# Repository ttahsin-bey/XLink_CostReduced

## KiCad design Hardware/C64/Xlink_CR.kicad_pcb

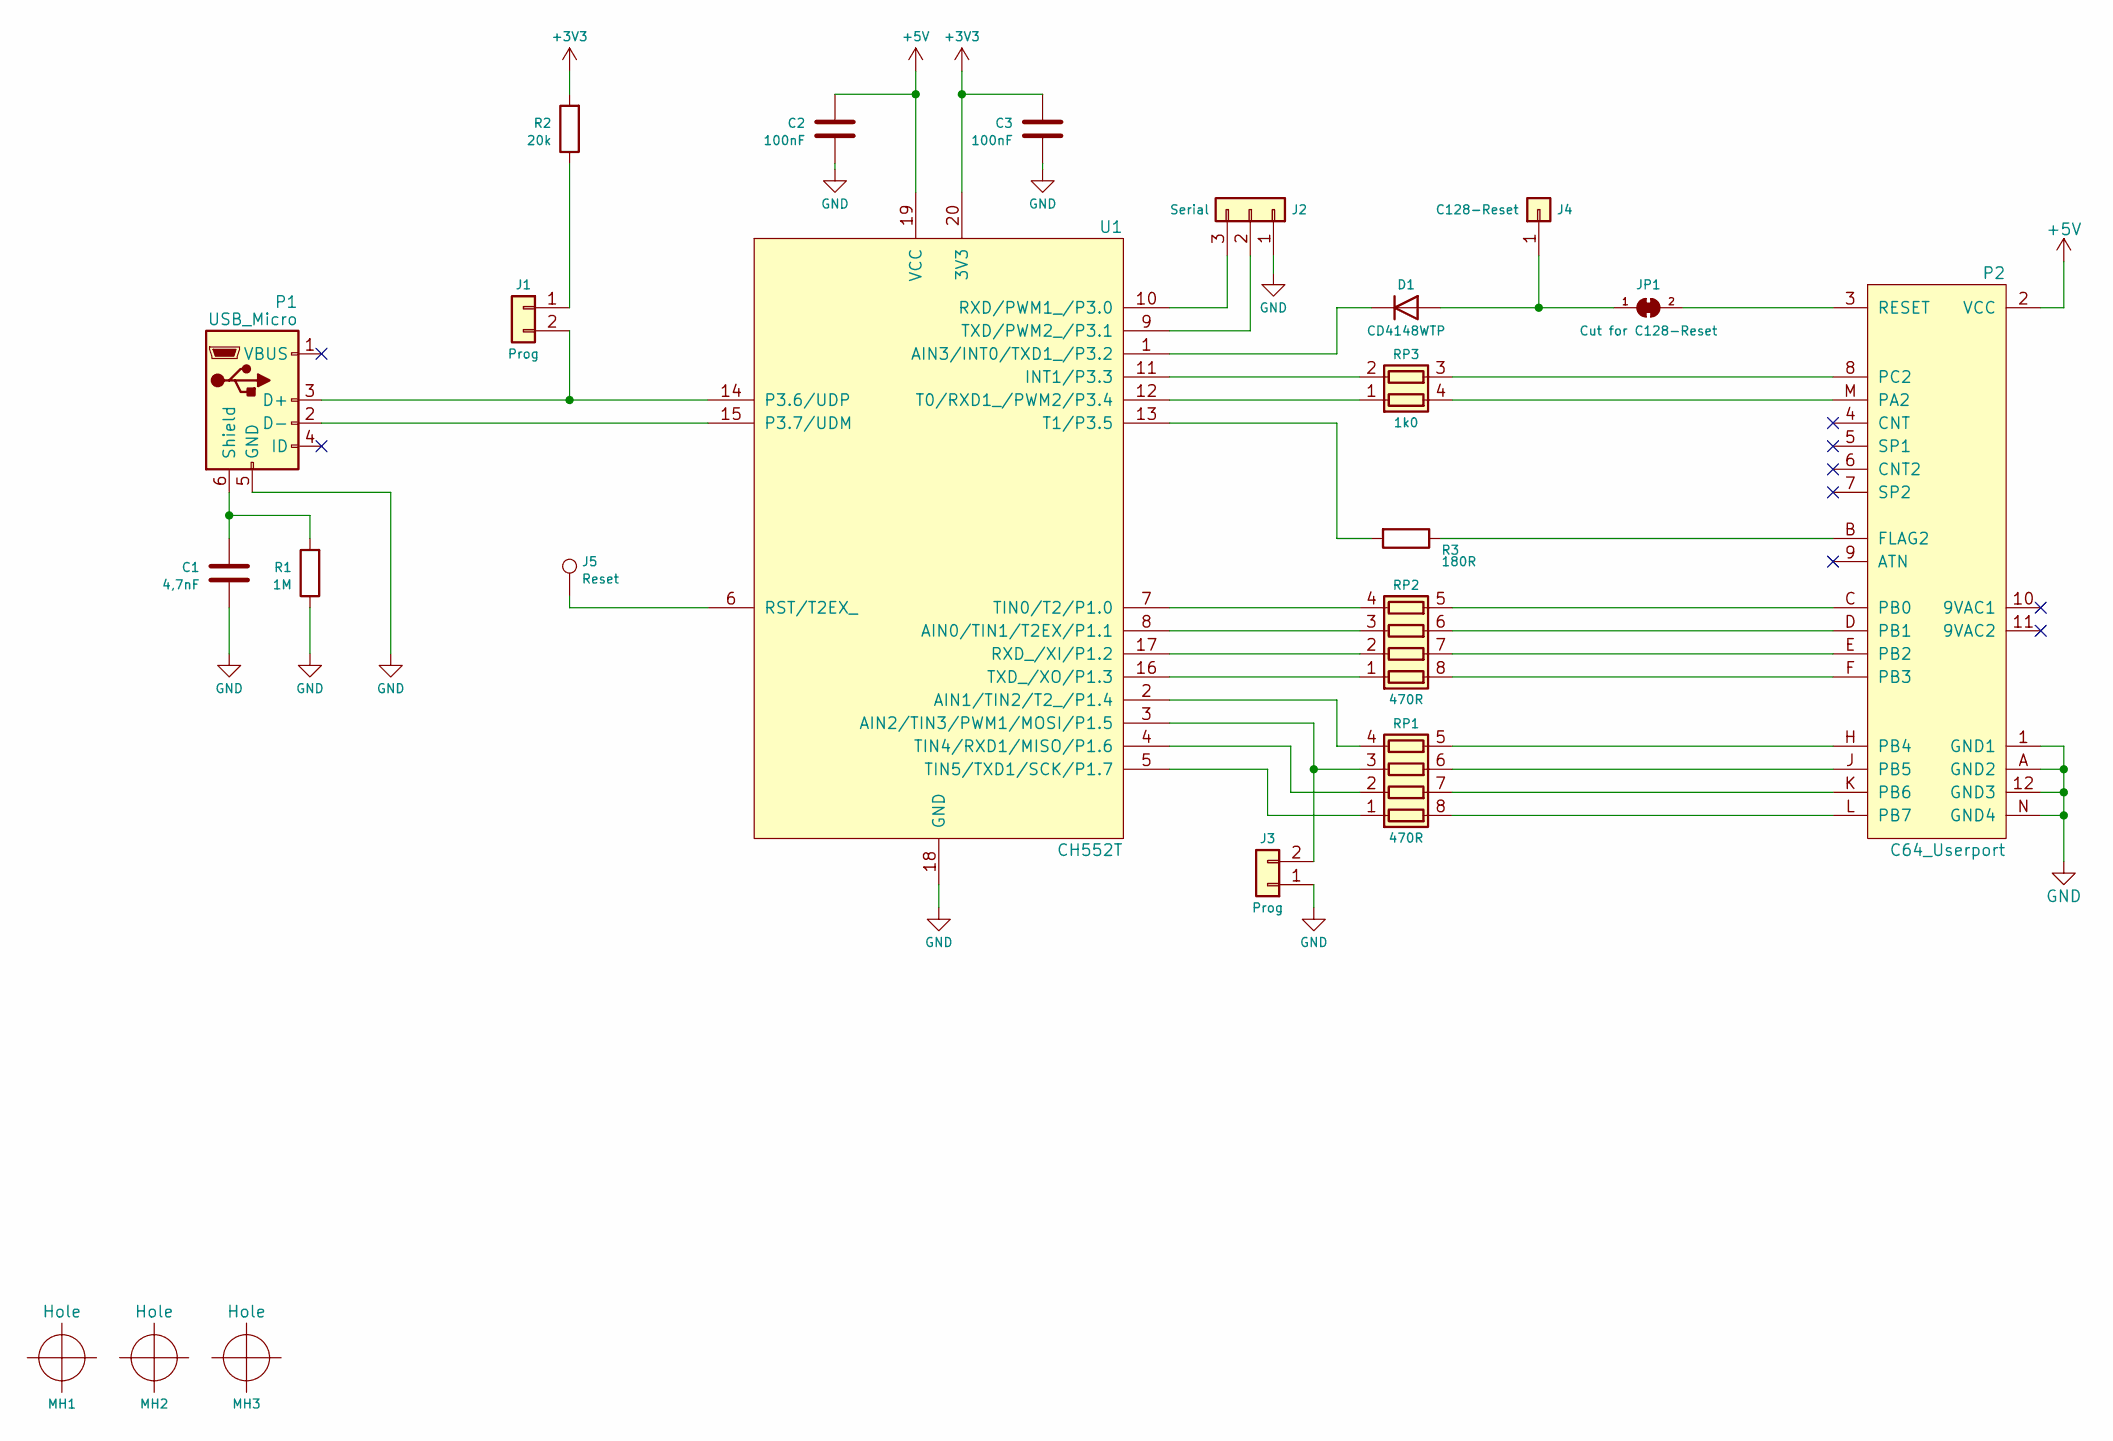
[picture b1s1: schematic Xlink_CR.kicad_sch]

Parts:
C1: 4,7nF; TTB_C0603; LCSC C106218
C2, C3: 100nF; TTB_C0603; LCSC C14663
D1: CD4148WTP; TTB_D0603; LCSC C109002
J1: Prog; TTB_Pinhead_2x1_2mm
J2: Serial; TTB_Pinhead_1x3_Rahmen
J3: Prog; TTB_Pinhead_1x2_Rahmen
J4: C128-Reset; TTB_Pinhead_1x1_Rahmen
J5: Reset; Measurement_Point_Round-SMD-Pad_Small
JP1: Cut for C128-Reset; SolderJumper-2_P1.3mm_Bridged_Pad1.0x1.5mm
MH1, MH2, MH3: Hole; MountingHole_3mm
P1: USB_Micro; TTB_USB-B_Micro_LCSC_C10418; LCSC C10418
P2: C64_Userport; TTB_C64_Userport
R1: 1M; TTB_R0603; LCSC C105578
R2: 20k; TTB_R0603; LCSC C105575
R3: 180R; TTB_R0603
RP1, RP2: 470R; TTB_RNet1206_4R; LCSC C102671
RP3: 1k0; TTB_RNet1206_2R
U1: CH552T; TSSOP-20_4.4x6.5mm_Pitch0.65mm; LCSC C111367

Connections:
+3V3: C3.2, R2.2, U1.20 (3V3)
+5V: C2.2, P2.2 (VCC), U1.19 (VCC)
GND: C1.1, C2.1, C3.1, J2.1, J3.1, P1.5 (GND), P2.1 (GND1), P2.12 (GND3), P2.A (GND2), P2.N (GND4), R1.1, U1.18 (GND)
unnamed: C1.2, P1.6 (Shield), R1.2
unnamed: D1.1 (K), U1.1 (AIN3/INT0/TXD1_/P3.2)
unnamed: D1.2 (A), J4.1, JP1.1 (A)
unnamed: J1.1, R2.1
unnamed: J1.2, P1.3 (D+), U1.14 (P3.6/UDP)
unnamed: J2.2, U1.9 (TXD/PWM2_/P3.1)
unnamed: J2.3, U1.10 (RXD/PWM1_/P3.0)
unnamed: J3.2, RP1.3 (R3.1), U1.3 (AIN2/TIN3/PWM1/MOSI/P1.5)
unnamed: J5.1, U1.6 (RST/T2EX_)
unnamed: JP1.2 (B), P2.3 (RESET)
unnamed: P1.2 (D-), U1.15 (P3.7/UDM)
unnamed: P2.8 (PC2), RP3.3 (R2.2)
unnamed: P2.B (FLAG2), R3.1
unnamed: P2.C (PB0), RP2.5 (R4.2)
unnamed: P2.D (PB1), RP2.6 (R3.2)
unnamed: P2.E (PB2), RP2.7 (R2.2)
unnamed: P2.F (PB3), RP2.8 (R1.2)
unnamed: P2.H (PB4), RP1.5 (R4.2)
unnamed: P2.J (PB5), RP1.6 (R3.2)
unnamed: P2.K (PB6), RP1.7 (R2.2)
unnamed: P2.L (PB7), RP1.8 (R1.2)
unnamed: P2.M (PA2), RP3.4 (R1.2)
unnamed: R3.2, U1.13 (T1/P3.5)
unnamed: RP1.1 (R1.1), U1.5 (TIN5/TXD1/SCK/P1.7)
unnamed: RP1.2 (R2.1), U1.4 (TIN4/RXD1/MISO/P1.6)
unnamed: RP1.4 (R4.1), U1.2 (AIN1/TIN2/T2_/P1.4)
unnamed: RP2.1 (R1.1), U1.16 (TXD_/XO/P1.3)
unnamed: RP2.2 (R2.1), U1.17 (RXD_/XI/P1.2)
unnamed: RP2.3 (R3.1), U1.8 (AIN0/TIN1/T2EX/P1.1)
unnamed: RP2.4 (R4.1), U1.7 (TIN0/T2/P1.0)
unnamed: RP3.1 (R1.1), U1.12 (T0/RXD1_/PWM2/P3.4)
unnamed: RP3.2 (R2.1), U1.11 (INT1/P3.3)

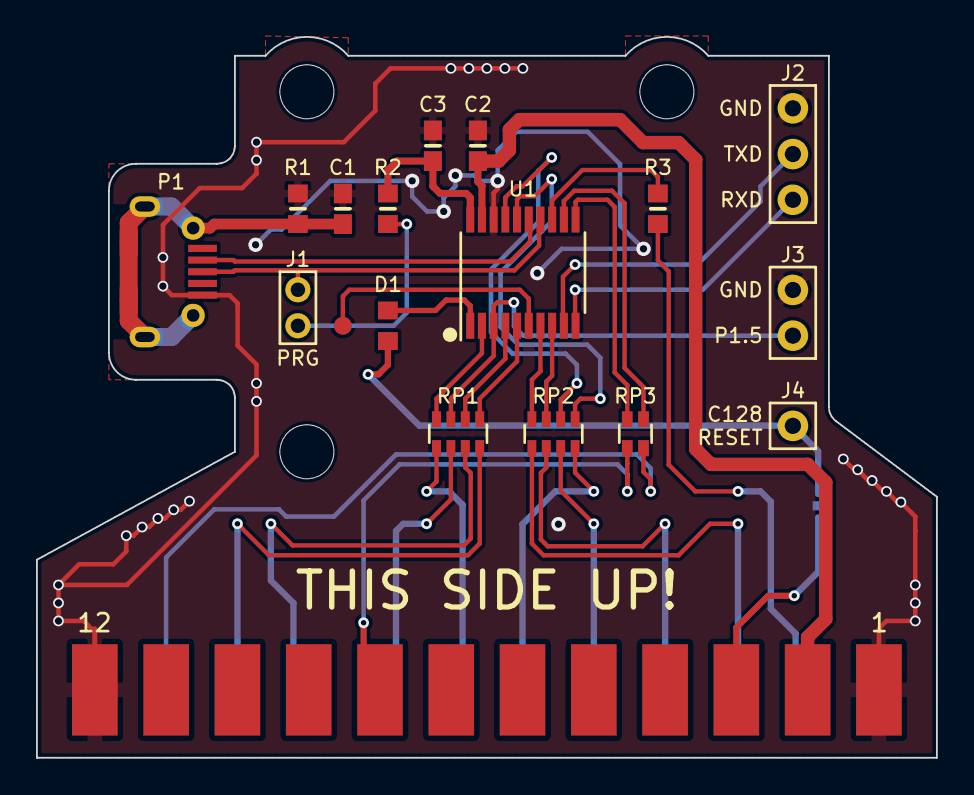
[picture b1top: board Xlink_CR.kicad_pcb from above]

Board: 2 copper layers, 50.0 x 40.0 mm, 22 parts (1 on the bottom side), 35 nets.

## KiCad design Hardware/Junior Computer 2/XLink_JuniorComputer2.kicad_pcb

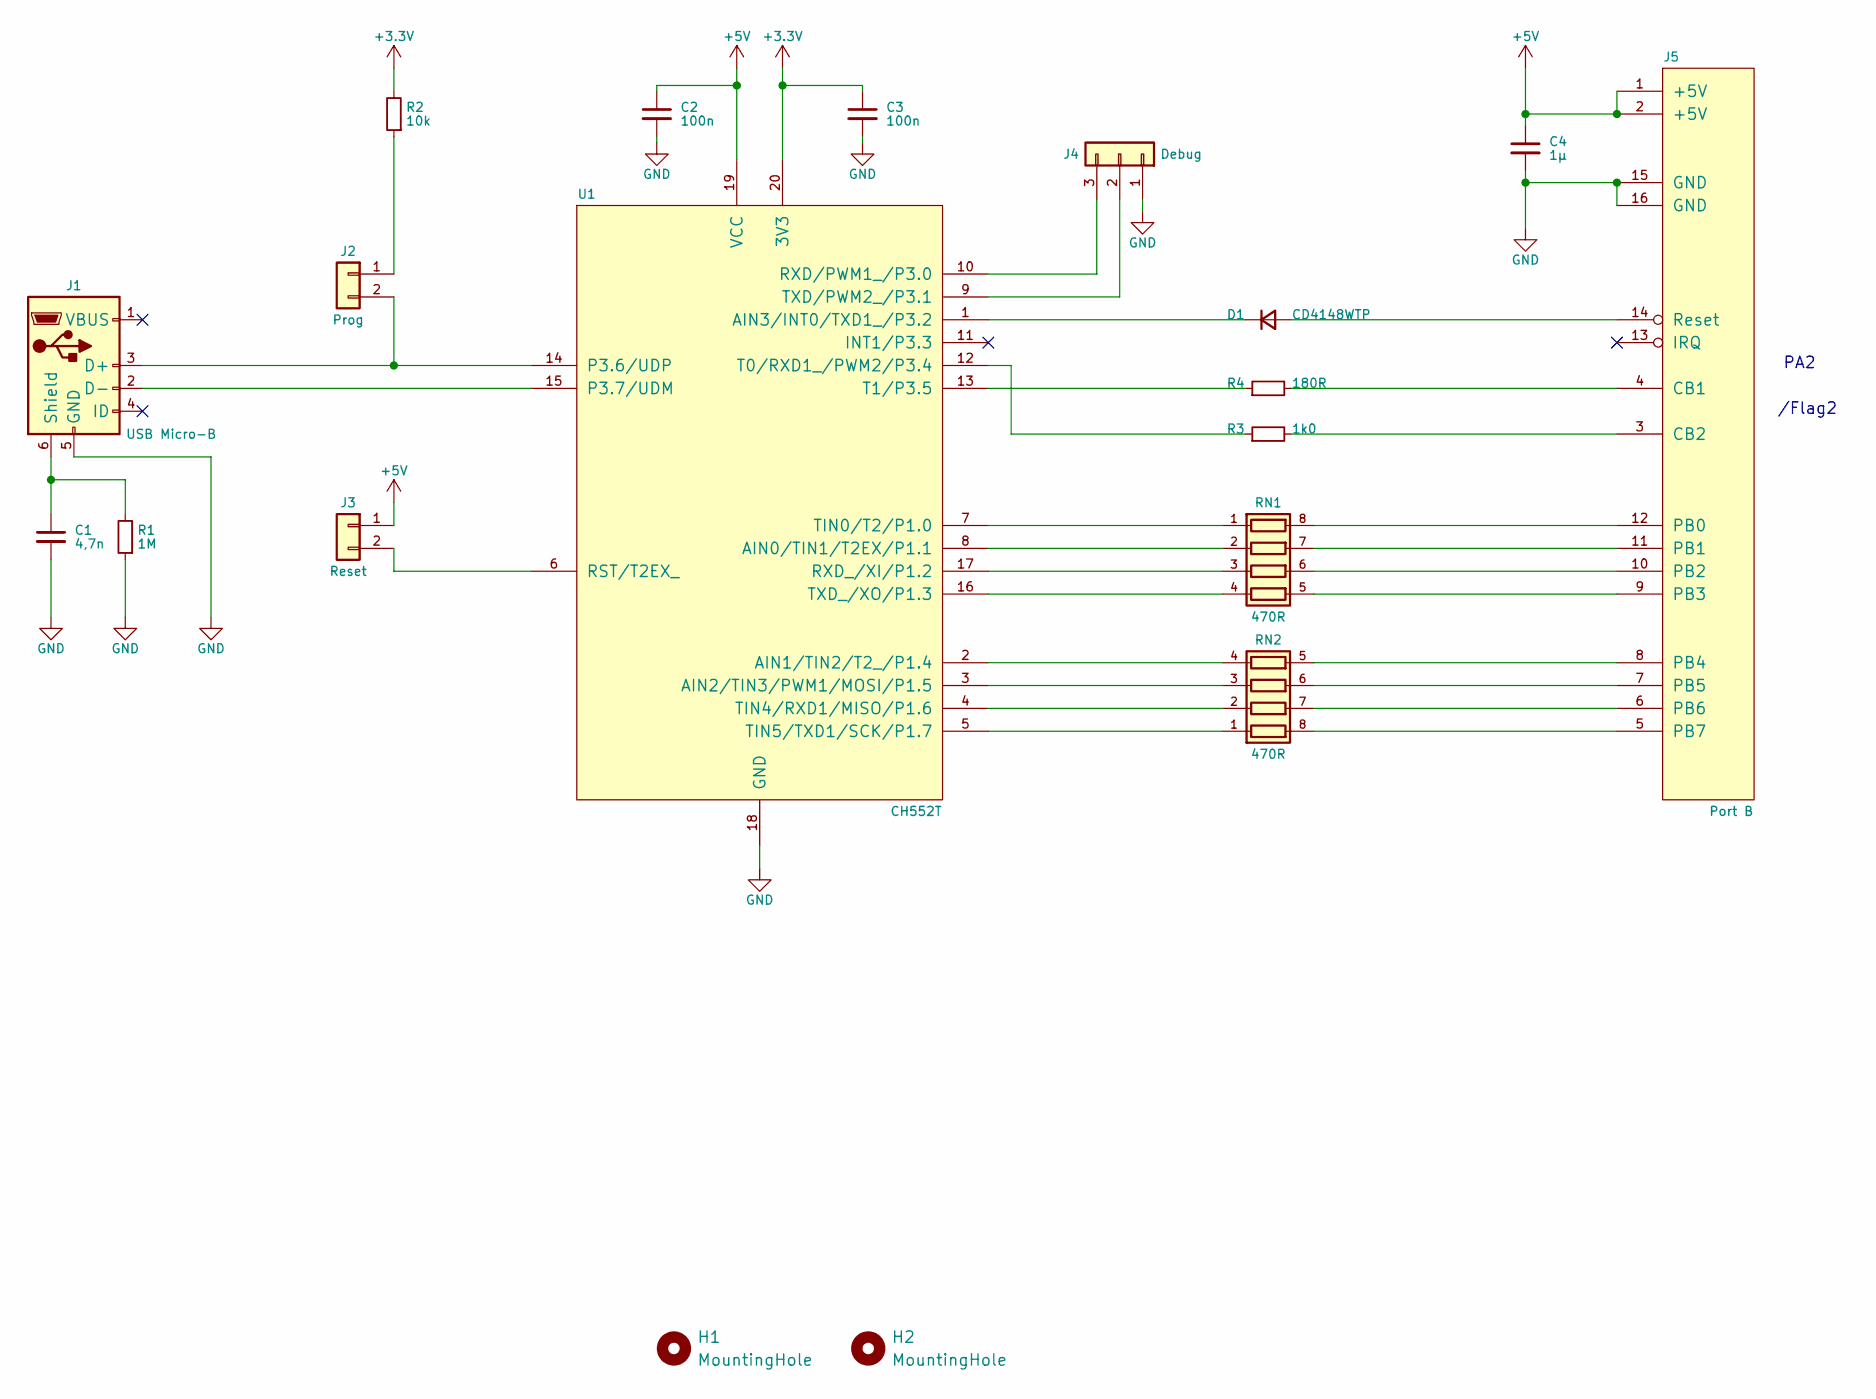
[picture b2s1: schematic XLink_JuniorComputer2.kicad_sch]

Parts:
C1: 4,7n; TTB_C0603; JLCPCB C53987
C2, C3: 100n; TTB_C0603; JLCPCB C30926
C4: 1µ; TTB_C0603; JLCPCB C59302
D1: CD4148WTP; TTB_D0603; JLCPCB C109002
H1, H2: MountingHole; MountingHole_2.7mm_M2.5_DIN965
J1: USB Micro-B; TTB_USB-B_Micro_LCSC_C10418; JLCPCB C10418
J2: Prog; TTB_Pinhead_1x2_Rahmen; JLCPCB C152154
J3: Reset; TTB_Pinhead_1x2_Rahmen; JLCPCB C152154
J4: Debug; TTB_Pinhead_1x3_Rahmen; JLCPCB C152153
J5: Port B; PinSocket_2x08_P2.54mm_Horizontal; JLCPCB C52105
R1: 1M; TTB_R0603; JLCPCB C858907
R2: 10k; TTB_R0603; JLCPCB C105575
R3: 1k0; TTB_R0603; JLCPCB C22548
R4: 180R; TTB_R0603; JLCPCB C137786
RN1, RN2: 470R; TTB_RNet1206_4R; JLCPCB C102671
U1: CH552T; TSSOP-20_4.4x6.5mm_P0.65mm; JLCPCB C111367

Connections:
+3.3V: C3.1, R2.2, U1.20 (3V3)
+5V: C2.1, C4.1, J3.1, J5.1 (+5V), J5.2 (+5V), U1.19 (VCC)
GND: C1.2, C2.2, C3.2, C4.2, J1.5 (GND), J4.1, J5.15 (GND), J5.16 (GND), R1.1, U1.18 (GND)
unnamed: C1.1, J1.6 (Shield), R1.2
unnamed: D1.1 (K), U1.1 (AIN3/INT0/TXD1_/P3.2)
unnamed: D1.2 (A), J5.14 (Reset)
unnamed: J1.2 (D-), U1.15 (P3.7/UDM)
unnamed: J1.3 (D+), J2.2, U1.14 (P3.6/UDP)
unnamed: J2.1, R2.1
unnamed: J3.2, U1.6 (RST/T2EX_)
unnamed: J4.2, U1.9 (TXD/PWM2_/P3.1)
unnamed: J4.3, U1.10 (RXD/PWM1_/P3.0)
unnamed: J5.3 (CB2), R3.2
unnamed: J5.4 (CB1), R4.2
unnamed: J5.5 (PB7), RN2.8 (R1.2)
unnamed: J5.6 (PB6), RN2.7 (R2.2)
unnamed: J5.7 (PB5), RN2.6 (R3.2)
unnamed: J5.8 (PB4), RN2.5 (R4.2)
unnamed: J5.9 (PB3), RN1.5 (R4.2)
unnamed: J5.10 (PB2), RN1.6 (R3.2)
unnamed: J5.11 (PB1), RN1.7 (R2.2)
unnamed: J5.12 (PB0), RN1.8 (R1.2)
unnamed: R3.1, U1.12 (T0/RXD1_/PWM2/P3.4)
unnamed: R4.1, U1.13 (T1/P3.5)
unnamed: RN1.1 (R1.1), U1.7 (TIN0/T2/P1.0)
unnamed: RN1.2 (R2.1), U1.8 (AIN0/TIN1/T2EX/P1.1)
unnamed: RN1.3 (R3.1), U1.17 (RXD_/XI/P1.2)
unnamed: RN1.4 (R4.1), U1.16 (TXD_/XO/P1.3)
unnamed: RN2.1 (R1.1), U1.5 (TIN5/TXD1/SCK/P1.7)
unnamed: RN2.2 (R2.1), U1.4 (TIN4/RXD1/MISO/P1.6)
unnamed: RN2.3 (R3.1), U1.3 (AIN2/TIN3/PWM1/MOSI/P1.5)
unnamed: RN2.4 (R4.1), U1.2 (AIN1/TIN2/T2_/P1.4)

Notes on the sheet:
PA2
/Flag2

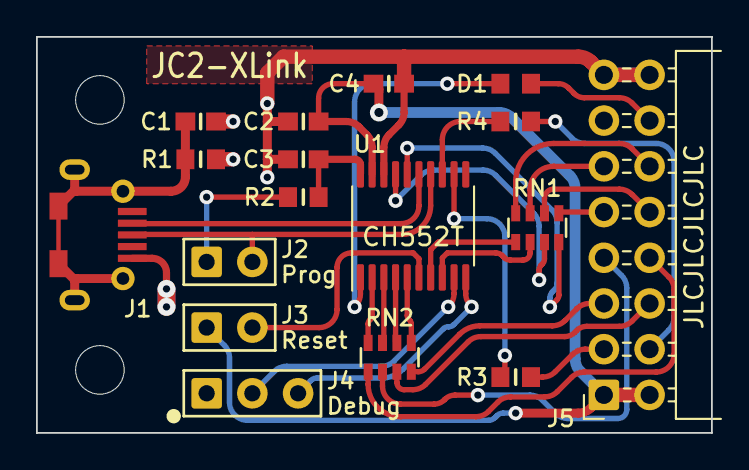
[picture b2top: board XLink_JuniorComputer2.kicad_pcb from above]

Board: 2 copper layers, 37.5 x 22.0 mm, 19 parts (0 on the bottom side), 32 nets.

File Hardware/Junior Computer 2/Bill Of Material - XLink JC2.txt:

Ref	Product		Package	Value				Distri	Order-Code

R1	Resistor	0603	1M, 1/10W,1%			LCSC	C22935
R2	Resistor	0603	10k, 1/10W, 1%			LCSC	C25804
R3	Resistor	0603	1k0, 1/10W, 1%			LCSC	C21190
R4	Resistor	0603	180R, 1/10W, 1%			LCSC	C22828

RN1	R-Network	1206	470R *4				LCSC	C1731350
RN2	R-Network	1206	470R *4				LCSC	C1731350

C1	Capacitor	0603	4.7nF/50V, X7R, MLCC		LCSC	C106218
C2	Capacitor	0603	100nF/50V, X7R, MLCC		LCSC	C14663
C3	Capacitor	0603	100nF/50V, X7R, MLCC		LCSC	C14663
C4	Capacitor	0603	1.0µF/50V, X7R, MLCC		LCSC	C559769

D1	Diode		0603	CD4148WTP			LCSC	C109002

U1	Microcontroller	TSSOP20	CH552T				LCSC	C111367

J1	USB-Connector	-	Micro-B 2.0, Female		LCSC	C10418
J5	Connector	-	Con 2.54mm Female, angled, 2x8P	LCSC	C2936005

PCB	1,6mm / 2 Layers					JLCPCB

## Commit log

2022-12-07 changed directory name: PCB --> Hardware
2022-12-10 Updated C64-PCB, added pictures
2022-12-10 added Readme
2022-12-10 added more Pictures
2022-12-17 Bill Of Material added
